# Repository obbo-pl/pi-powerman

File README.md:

# Pi-Powerman
  The main goal is to create a universal service operating with Raspberry Pi allowing you to control the power system. Of course, the power supply must be compatible in terms of how to communicate with the service. The current version uses I2C and two I/O ports for this purpose. The solution consists of: a service running on Raspberry and a microcontroller power supply co-operating with it. 

##### Main features:
- Easy adaptation of the power supply system,
- UPS function, automatic switching to backup power supply, battery charging and charging status monitoring,
- Automatic "shutdown" after power loss,
- Up to 8 buttons with LED (1 power button and 7 user defined),
- Ability to define extended scenarios for buttons,
- LEDs automatically indicate the state of buttons and related scenarios,
- Up to 8 connected power circuits (including 1 dedicated for Raspberry Pi),
- Cut off the power after shutting down the system,
- Monitoring of voltage, power consumption, UPS status, temperature and battery voltage,
- Export of monitored values to RRD and .txt files, .csv,
- IoT, sending messages by the MQTT protocol, 
- Communication with Raspberry via I2C and two dedicated I/O ports,
- Dedicated LED for power and Raspberry status indication.

### Requirements:
- Python 3
- Raspbian Jessie or newer

### Installation:
```
sudo apt-get update
sudo apt-get install python3-yaml python3-pip librrd-dev
sudo python3 -m pip install RPi.GPIO smbus rrdtool schedule paho-mqtt

cd /tmp
wget https://www.obbo.pl/files/articles/pi-powerman/pi-powerman.tgz
sudo mkdir /usr/local/pi-powerman
sudo tar -xf pi-powerman.tgz -C /usr/local/pi-powerman/

cd /etc/systemd/system/ 
sudo ln -s /usr/local/pi-powerman/pi-powerman.service pi-powerman.service

sudo systemctl daemon-reload
sudo systemctl enable pi-powerman.service
sudo systemctl start pi-powerman.service
```

### Hardware & Firmware.
These sections covers info on building sample hardware, including schematics, PCBs, and the corresponding firmware.

For more information: [www.obbo.pl](http://www.obbo.pl/pi-powerman)

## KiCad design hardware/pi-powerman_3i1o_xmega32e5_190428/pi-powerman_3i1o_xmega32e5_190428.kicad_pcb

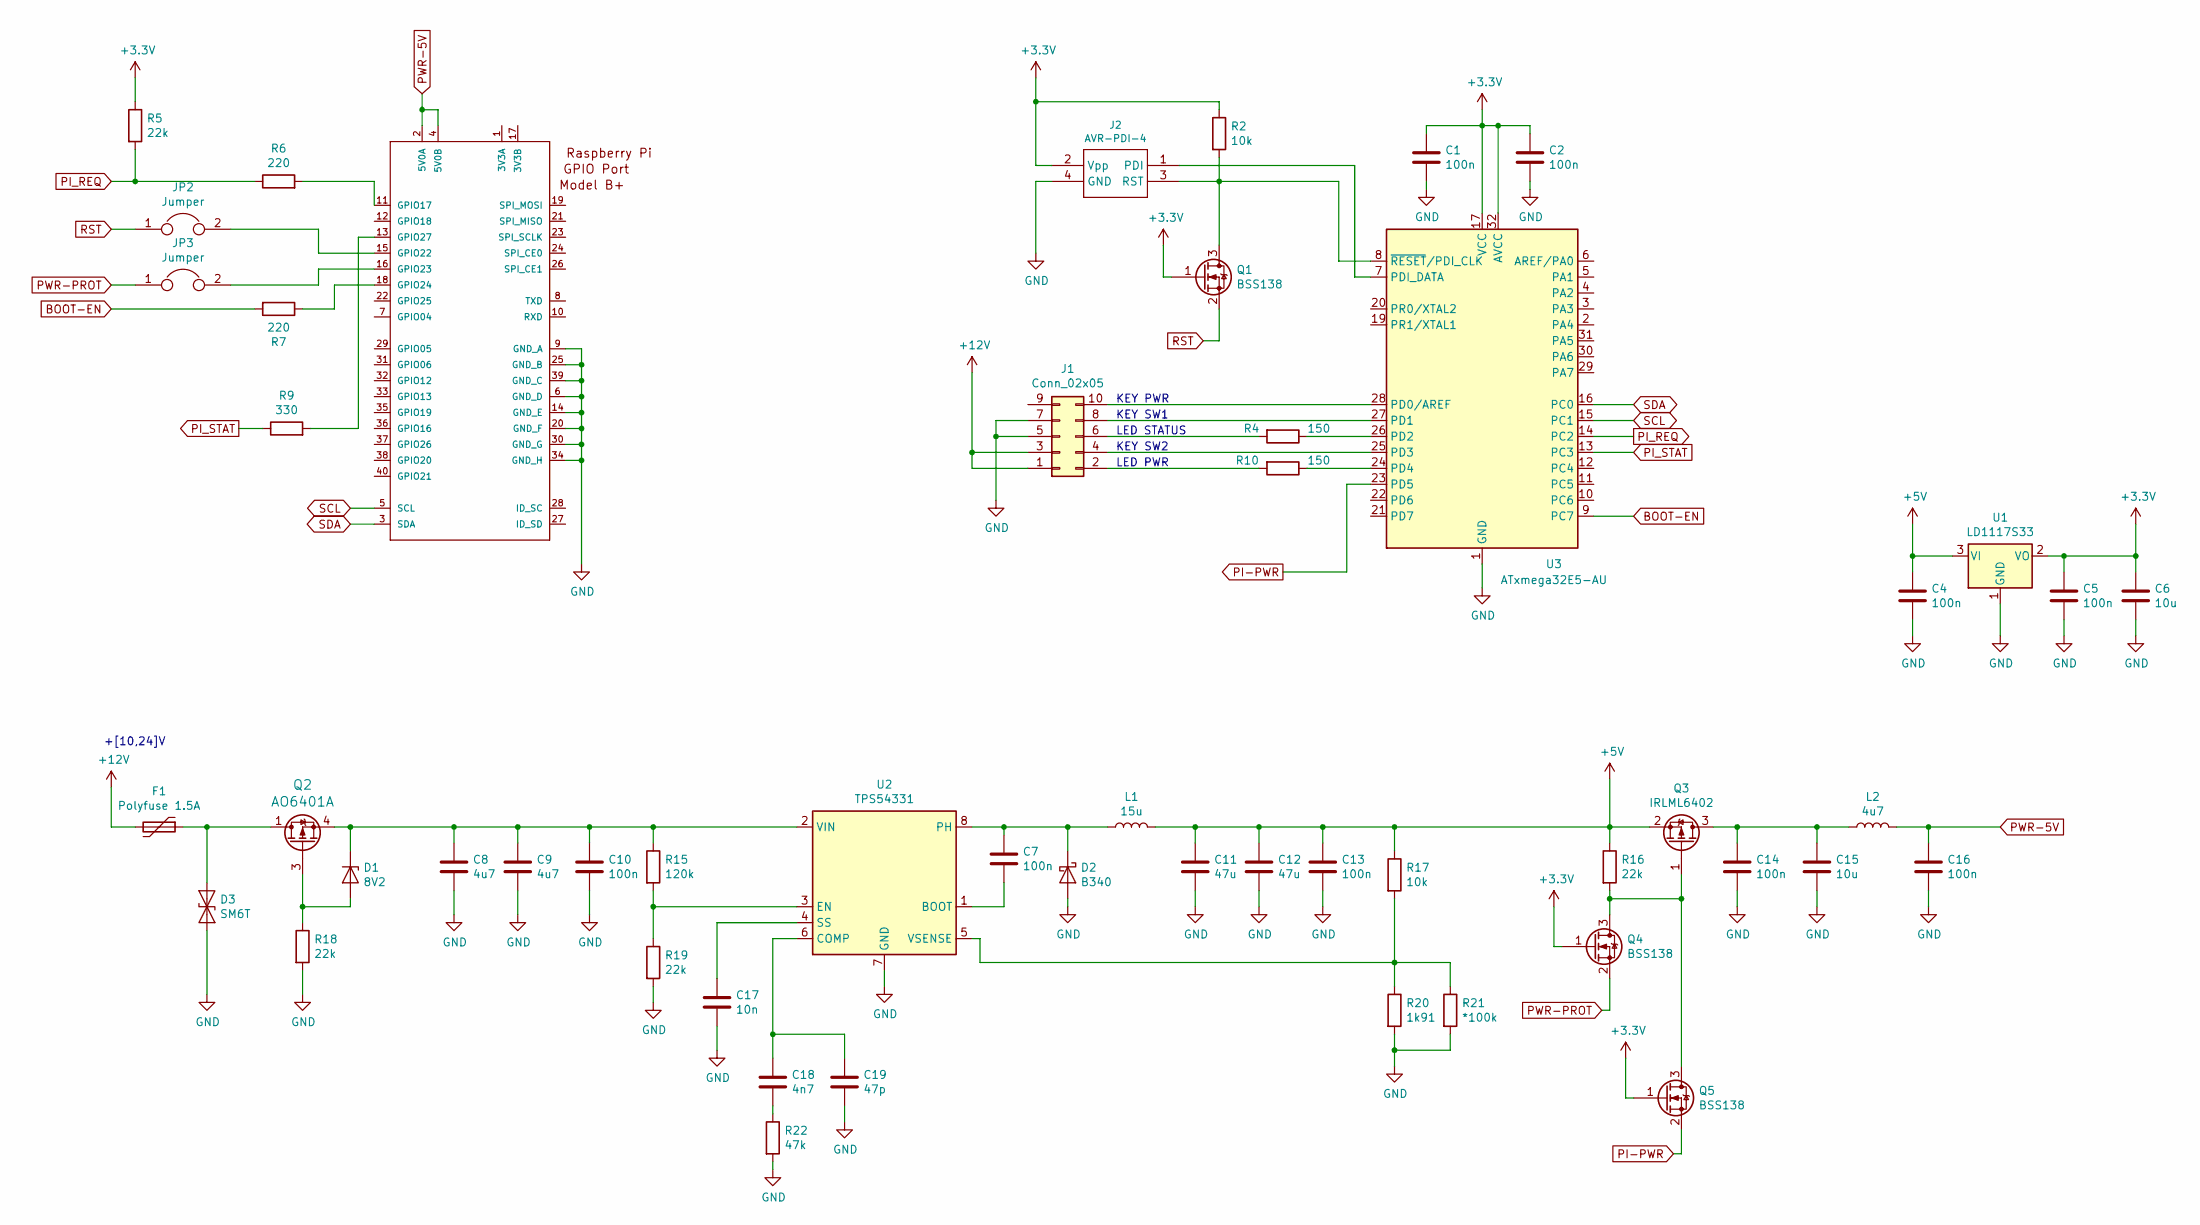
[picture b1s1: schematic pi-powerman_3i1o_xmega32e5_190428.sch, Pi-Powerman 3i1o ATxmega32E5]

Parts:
C1, C2, C4, C5, C10, C13, C16: 100n; C_Disc_D5.0mm_W2.5mm_P5.00mm_PAD
C6, C15: 10u; C_1206_3216Metric_Pad1.42x1.75mm_HandSolder
C7, C14: 100n; C_0805K
C8, C9: 4u7; C_1210_3225Metric_Pad1.42x2.65mm_HandSolder
C11, C12: 47u; C_1210_3225Metric_Pad1.42x2.65mm_HandSolder
C17: 10n; C_0805K
C18: 4n7; C_0805K
C19: 47p; C_0805K
CON1: RASPI_HAT_GPIO_B+-I2S; raspberrypi_RASPI_BOARD_B+HAT_SMD_V01
D1: 8V2; D_MiniMELF
D2: B340; D_SMA
D3: SM6T; D_SMB
F1: Polyfuse 1.5A; F_1812_4532Metric_Pad1.30x3.40mm_HandSolder
J1: Conn_02x05; IDC-Header_2x05_P2.54mm_SMD_Horizontal_Edge
J2: AVR-PDI-4; PinHeader_2x02_P2.54mm_Vertical_SMD
JP2, JP3: Jumper; PinHeader_1x02_P2.54mm_Horizontal_PAD
L1: 15u; L_SMD_Ferrite_X7mm_Y7mm_H4.5mm_HandSoldering
L2: 4u7; L_SMD_Ferrite_X5mm_Y5mm_H4mm_HandSoldering
Q1, Q4, Q5: BSS138; SOT-23
Q2: AO6401A; TSOP-6_1.65x3.05mm_P0.95mm
Q3: IRLML6402; SOT-23
R2, R17: 10k; R_0805K
R4, R10: 150; R_0805K
R5, R16, R18, R19: 22k; R_0805K
R6, R7: 220; R_0805K
R9: 330; R_0805K
R15: 120k; R_0805K
R20: 1k91; R_0805K
R21: *100k; R_0805K
R22: 47k; R_0805K
U1: LD1117S33; SOT-223-3_TabPin2
U2: TPS54331; SOIC-8_3.9x4.9mm_P1.27mm
U3: ATxmega32E5-AU; TQFP-32_7x7mm_P0.8mm

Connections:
+3V3: C1.1, C2.1, C5.1, C6.1, J2.2 (Vpp), Q1.1 (G), Q4.1 (G), Q5.1 (G), R2.1, R5.1, U1.2 (VO), U3.17 (VCC), U3.32 (AVCC)
+5V: C4.1, C11.1, C12.1, C13.1, L1.2, Q3.2 (S), R16.1, R17.1, U1.3 (VI)
+12V: F1.2, J1.1, J1.3
BOOT-EN: R7.2, U3.9 (PC7)
GND: C1.2, C2.2, C4.2, C5.2, C6.2, C8.2, C9.2, C10.2, C11.2, C12.2, C13.2, C14.2, C15.2, C16.2, C17.2, C19.2, CON1.6 (GND_D), CON1.9 (GND_A), CON1.14 (GND_E), CON1.20 (GND_F), CON1.25 (GND_B), CON1.30 (GND_G), CON1.34 (GND_H), CON1.39 (GND_C), D2.2 (A), D3.2 (A2), J1.5, J1.7, J2.4 (GND), R18.2, R19.2, R20.2, R21.2, R22.2, U1.1 (GND), U2.7 (GND), U3.1 (GND), U3.18 (GND)
unnamed: C7.1, D2.1 (K), L1.1, U2.8 (PH)
unnamed: C7.2, U2.1 (BOOT)
unnamed: C8.1, C9.1, C10.1, D1.1 (K), Q2.4 (S), R15.1, U2.2 (VIN)
unnamed: C14.1, C15.1, L2.1, Q3.3 (D)
unnamed: C17.1, U2.4 (SS)
unnamed: C18.1, C19.1, U2.6 (COMP)
unnamed: C18.2, R22.1
unnamed: CON1.11 (GPIO17), R6.2
unnamed: CON1.13 (GPIO27), R9.2
unnamed: CON1.15 (GPIO22), JP2.2
unnamed: CON1.16 (GPIO23), JP3.2
unnamed: CON1.18 (GPIO24), R7.1
unnamed: D1.2 (A), Q2.3 (G), R18.1
unnamed: D3.1 (A1), F1.1, Q2.1 (D), Q2.2 (D), Q2.5 (D), Q2.6 (D)
unnamed: J1.2, R10.2
unnamed: J1.4, U3.25 (PD3)
unnamed: J1.6, R4.2
unnamed: J1.8, U3.27 (PD1)
unnamed: J1.10, U3.28 (PD0/AREF)
unnamed: J2.1 (PDI), U3.7 (PDI_DATA)
unnamed: J2.3 (RST), Q1.3 (D), R2.2, U3.8 (~RESET~/PDI_CLK)
unnamed: Q3.1 (G), Q4.3 (D), Q5.3 (D), R16.2
unnamed: R4.1, U3.26 (PD2)
unnamed: R10.1, U3.24 (PD4)
unnamed: R15.2, R19.1, U2.3 (EN)
unnamed: R17.2, R20.1, R21.1, U2.5 (VSENSE)
PI-PWR: Q5.2 (S), U3.23 (PD5)
PI_REQ: R5.2, R6.1, U3.14 (PC2)
PI_STAT: R9.1, U3.13 (PC3)
PWR-5V: C16.1, CON1.2 (5V0A), CON1.4 (5V0B), L2.2
PWR-PROT: JP3.1, Q4.2 (S)
RST: JP2.1, Q1.2 (S)
SCL: CON1.5 (SCL), U3.15 (PC1)
SDA: CON1.3 (SDA), U3.16 (PC0)

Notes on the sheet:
+[10,24]V
LED STATUS
LED PWR
KEY PWR
KEY SW1
KEY SW2

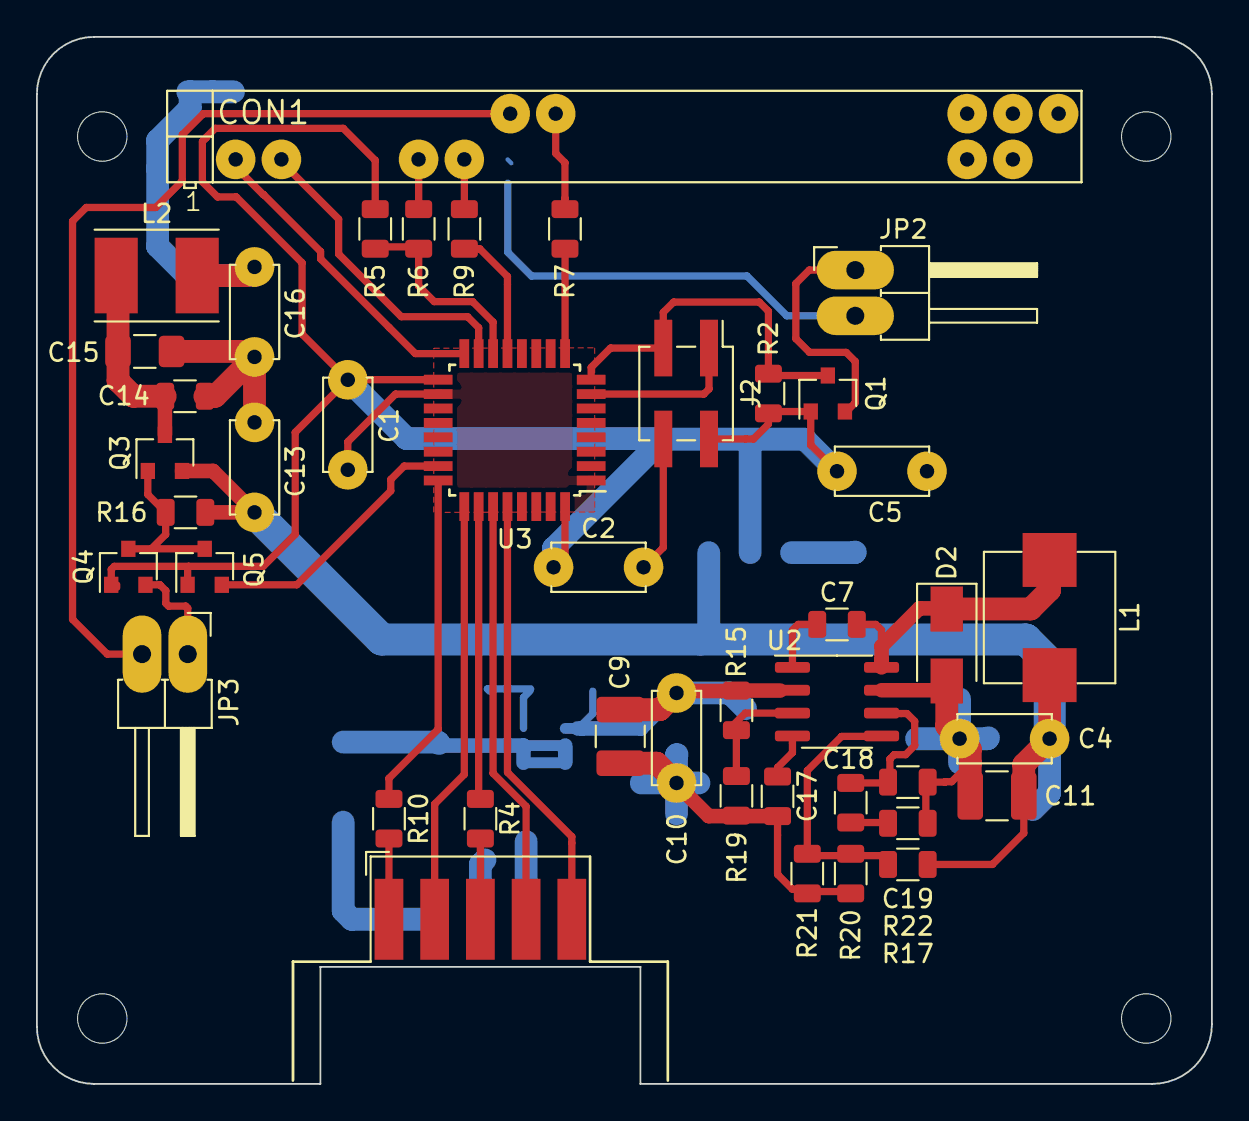
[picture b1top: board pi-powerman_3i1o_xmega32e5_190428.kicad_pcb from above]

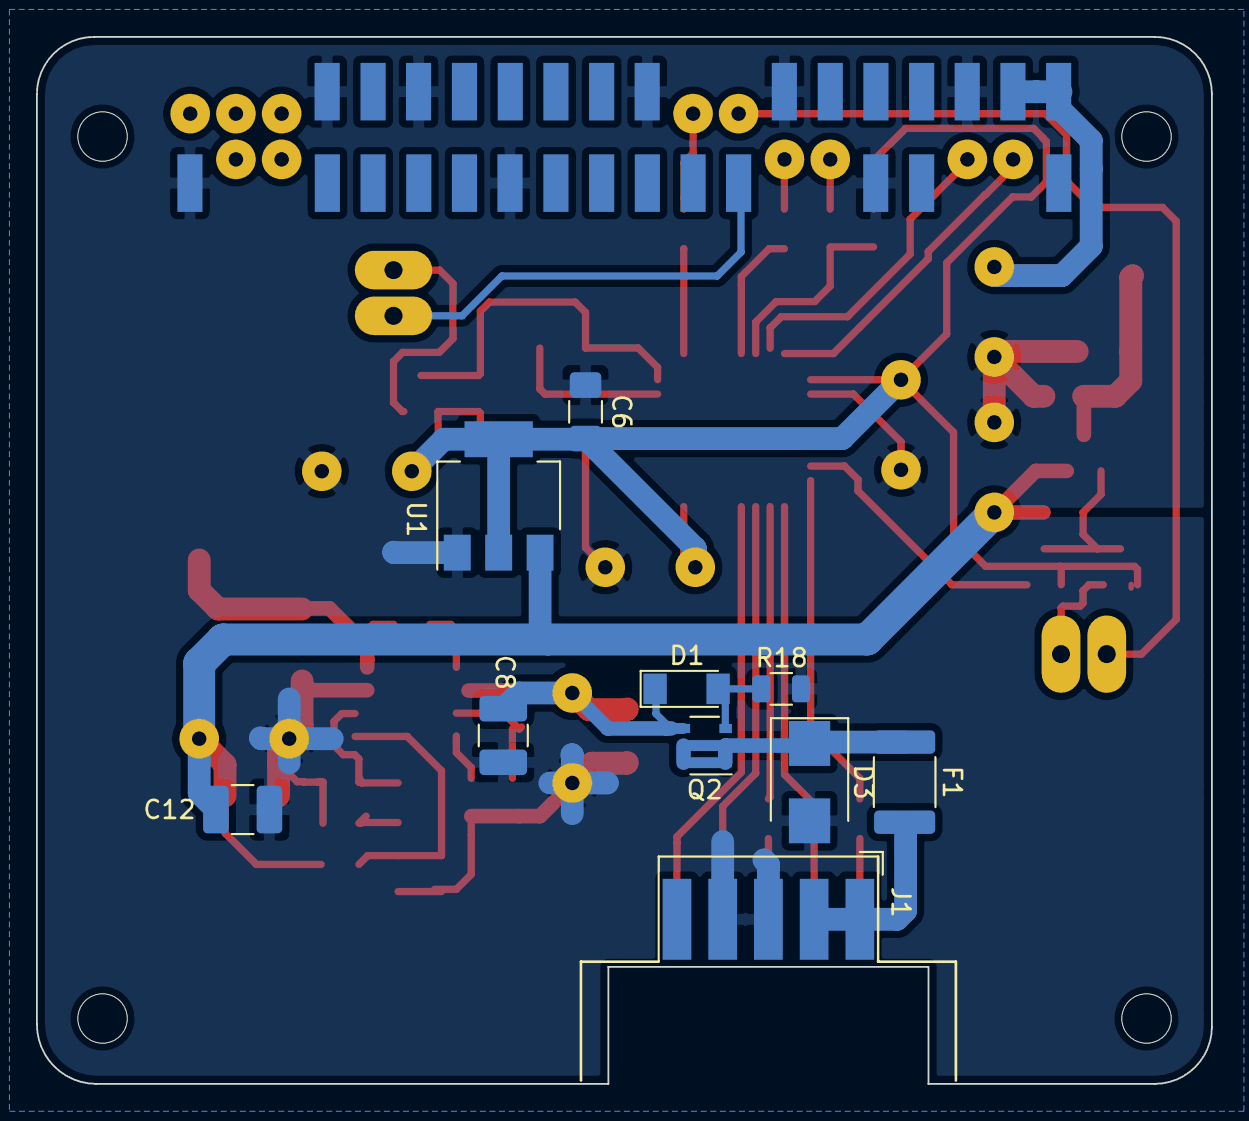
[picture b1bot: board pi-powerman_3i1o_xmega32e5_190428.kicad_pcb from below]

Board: 2 copper layers, 65.3 x 58.2 mm, 52 parts (10 on the bottom side), 39 nets.

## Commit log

2019-04-18 Update LICENSE
2019-04-22 example script
2019-04-26 upload
2019-04-27 schematic in .png
2019-04-28 move MQTT connect/disconnect to class PiPowerExport
2019-05-12 add UPS info
2019-05-18 change: OUTPUT_BUFFER_SIZE, change: command code
2019-05-18 change: data frame format
2019-05-19 add: hardware features info
2019-05-24 add: features recognition
2019-05-24 change: export functions
2019-06-05 change: in PiPowerData class
2019-06-06 move RRD to a separate class
2019-06-06 update configuration template
2019-06-07 new data format for publish over MQTT
2019-12-04 symbols update
2019-12-04 new sample hardware
2019-12-05 new options in setup and upgrade to support the latest firmware version
2019-12-05 configuration file support
